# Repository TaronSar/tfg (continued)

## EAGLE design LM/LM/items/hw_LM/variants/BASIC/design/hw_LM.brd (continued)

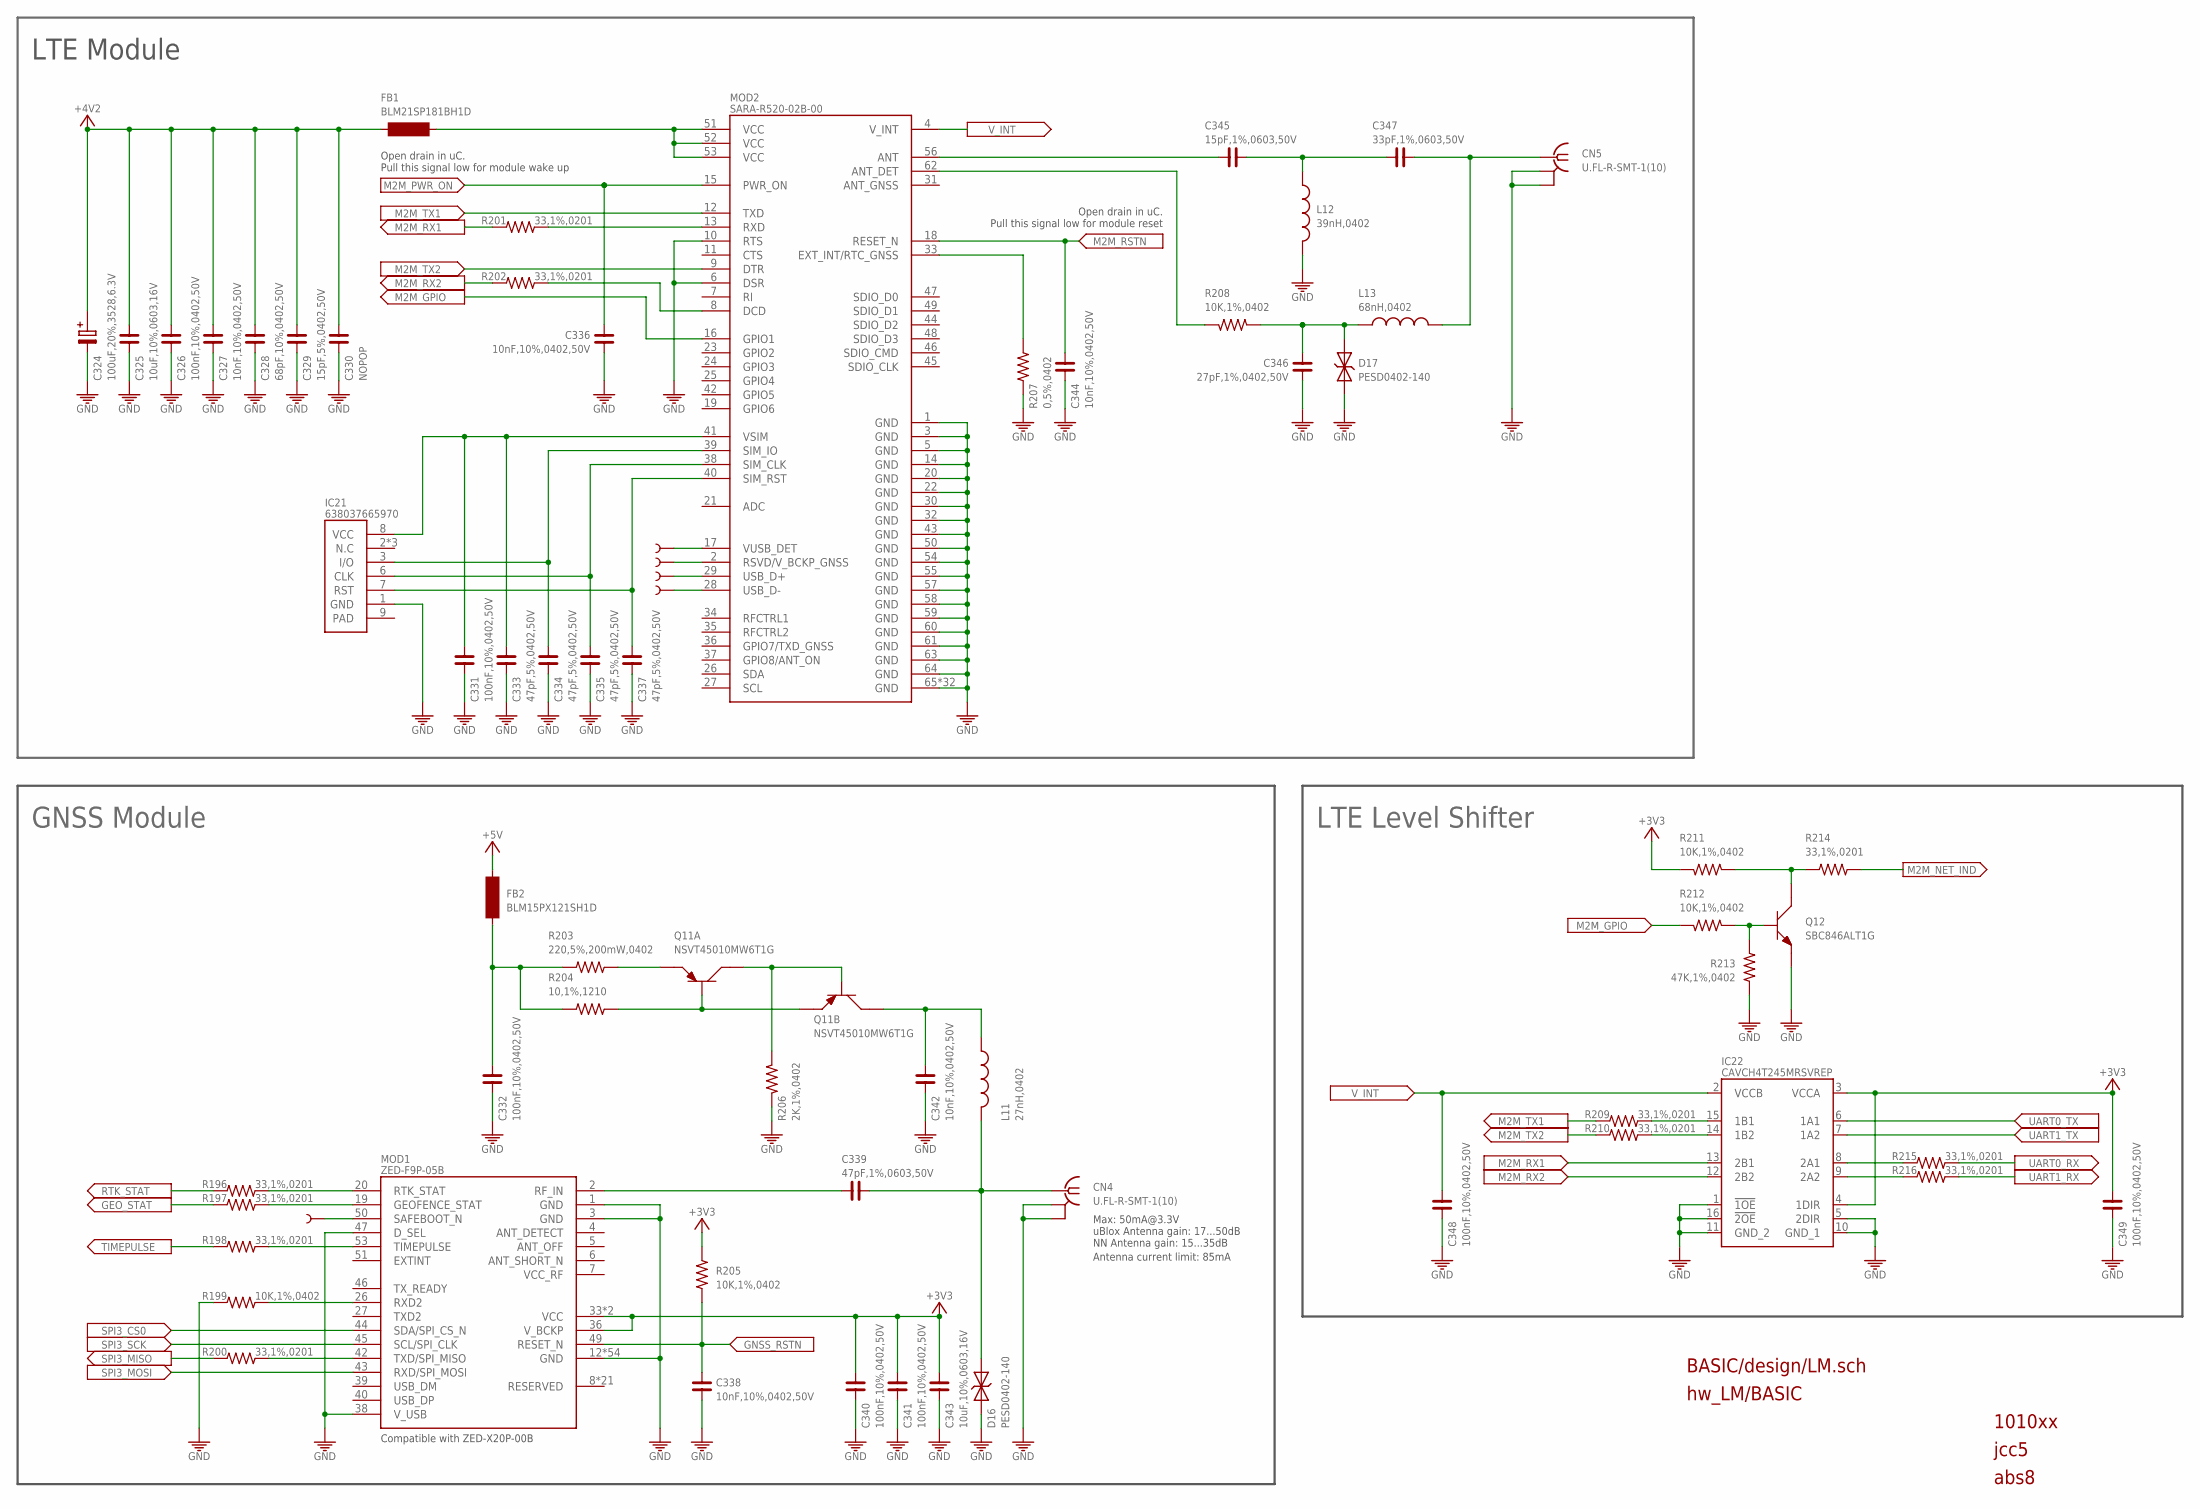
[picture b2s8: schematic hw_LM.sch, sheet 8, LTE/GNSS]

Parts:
C324: 100uF,20%,3528,6.3V; TE-B-3528
C325, C343: 10uF,10%,0603,16V; C0603
C326, C331, C332, C340, C341, C348, C349: 100nF,10%,0402,50V; C0402
C327, C336, C338, C342, C344: 10nF,10%,0402,50V; C0402
C328: 68pF,10%,0402,50V; C0402
C329: 15pF,5%,0402,50V; C0402
C330: NOPOP; C0402
C333, C334, C335, C337: 47pF,5%,0402,50V; C0402
C339: 47pF,1%,0603,50V; C0603
C345: 15pF,1%,0603,50V; C0603
C346: 27pF,1%,0402,50V; C0402
C347: 33pF,1%,0603,50V; C0603
CN4, CN5: U.FL-R-SMT-1(10); U.FL-R-SMT-1
D16, D17: PESD0402-140
FB1: BLM21SP181BH1D; L0805
FB2: BLM15PX121SH1D; L0402
IC21: 638037665970; MFF2
IC22: CAVCH4T245MRSVREP; UQFN-16
L11: 27nH,0402; L0402
L12: 39nH,0402; L0402
L13: 68nH,0402; L0402
MOD1: ZED-F9P-05B; ZED-F9P
MOD2: SARA-R520-02B-00; SARA
Q11: NSVT45010MW6T1G; SOT363
Q12: SBC846ALT1G; SOT23-3
R196, R197, R198, R200, R201, R202, R209, R210, R214, R215, R216: 33,1%,0201; R0201
R199, R205, R208, R211, R212: 10K,1%,0402; R0402
R203: 220,5%,200mW,0402; R0402
R204: 10,1%,1210; R1210
R206: 2K,1%,0402; R0402
R207: 0,5%,0402; R0402
R213: 47K,1%,0402; R0402
TP14, TP15, TP16, TP17, TP18: NOPOP; PAD.02X.02

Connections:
+3V3: C340.2, C341.2, C343.2, C349.2, IC22.3 (VCCA), IC22.4 (1DIR), MOD1.33 (VCC), MOD1.34 (VCC), MOD1.36 (V_BCKP), R205.1, R211.1; also elsewhere on the board
+4V2: C324.+, C325.2, C326.2, C327.2, C328.2, C329.2, C330.2, FB1.1; also elsewhere on the board
+5V: FB2.1; also elsewhere on the board
ANT_DC: C345.2, C347.1, L12.1
ANT_DET_SARA: MOD2.62 (ANT_DET), R208.2
ANT_OUT: C345.1, MOD2.56 (ANT)
GEO_STAT: R197.1; also elsewhere on the board
GND: C324.-, C325.1, C326.1, C327.1, C328.1, C329.1, C330.1, C331.2, C332.1, C333.2, C334.2, C335.2, C336.2, C337.2, C338.2, C340.1, C341.1, C342.1, C343.1, C344.2, C346.2, C348.1, C349.1, CN4.GND1 (GNDGPS), CN4.GND2 (GNDGPS1), CN5.GND1 (GNDGPS), CN5.GND2 (GNDGPS1), D16.P$1, D17.P$1, IC21.1 (GND), IC22.1 (!1OE), IC22.5 (2DIR), IC22.10 (GND_1), IC22.11 (GND_2), IC22.16 (!2OE), L12.2, MOD1.1 (GND), MOD1.3 (GND), MOD1.12 (GND), MOD1.14 (GND), MOD1.32 (GND), MOD1.37 (GND), MOD1.38 (V_USB), MOD1.41 (GND), MOD1.47 (D_SEL), MOD1.48 (GND), MOD1.GND1 (GND), MOD1.GND2 (GND), MOD1.GND3 (GND), MOD1.GND4 (GND), MOD1.GND5 (GND), MOD1.GND6 (GND), MOD1.GND7 (GND), MOD1.GND8 (GND), MOD1.GND9 (GND), MOD1.GND10 (GND), MOD1.GND11 (GND), MOD1.GND12 (GND), MOD1.GND13 (GND), MOD1.GND14 (GND), MOD1.GND15 (GND), MOD1.GND16 (GND), MOD1.GND17 (GND), MOD1.GND18 (GND), MOD1.GND19 (GND), MOD1.GND20 (GND), MOD1.GND21 (GND), MOD1.GND22 (GND), MOD1.GND23 (GND), MOD1.GND24 (GND), MOD1.GND25 (GND), MOD1.GND26 (GND), MOD1.GND27 (GND), MOD1.GND28 (GND), MOD1.GND29 (GND), MOD1.GND30 (GND), MOD1.GND31 (GND), MOD1.GND32 (GND), MOD1.GND33 (GND), MOD1.GND34 (GND), MOD1.GND35 (GND), MOD1.GND36 (GND), MOD1.GND37 (GND), MOD1.GND38 (GND), MOD1.GND39 (GND), MOD1.GND40 (GND), MOD1.GND41 (GND), MOD1.GND42 (GND), MOD1.GND43 (GND), MOD1.GND44 (GND), MOD1.GND45 (GND), MOD1.GND46 (GND), MOD1.GND47 (GND), MOD1.GND48 (GND), MOD2.1 (GND), MOD2.3 (GND), MOD2.5 (GND), MOD2.6 (DSR), MOD2.10 (RTS), MOD2.14 (GND), MOD2.20 (GND), MOD2.22 (GND), MOD2.30 (GND), MOD2.32 (GND), MOD2.43 (GND), MOD2.50 (GND), MOD2.54 (GND), MOD2.55 (GND), MOD2.57 (GND), MOD2.58 (GND), MOD2.59 (GND), MOD2.60 (GND), MOD2.61 (GND), MOD2.63 (GND), MOD2.64 (GND), MOD2.65 (GND), MOD2.66 (GND), MOD2.67 (GND), MOD2.68 (GND), MOD2.69 (GND), MOD2.70 (GND), MOD2.71 (GND), MOD2.72 (GND), MOD2.73 (GND), MOD2.74 (GND), MOD2.75 (GND), MOD2.76 (GND), MOD2.77 (GND), MOD2.78 (GND), MOD2.79 (GND), MOD2.80 (GND), MOD2.81 (GND), MOD2.82 (GND), MOD2.83 (GND), MOD2.84 (GND), MOD2.85 (GND), MOD2.86 (GND), MOD2.87 (GND), MOD2.88 (GND), MOD2.89 (GND), MOD2.90 (GND), MOD2.91 (GND), MOD2.92 (GND), MOD2.93 (GND), MOD2.94 (GND), MOD2.95 (GND), MOD2.96 (GND), Q12.2 (E), R199.1, R206.1, R207.1, R213.1; also elsewhere on the board
GNSS: C339.2, CN4.SIG, D16.P$2, L11.2
GNSS_RSTN: C338.1, MOD1.49 (RESET_N), R205.2; also elsewhere on the board
LTE: C347.2, CN5.SIG, L13.2
M2M_DCD: MOD2.8 (DCD), R202.2
M2M_GPIO: MOD2.16 (GPIO1), R212.2
M2M_NET_IND: R214.2; also elsewhere on the board
M2M_PWR_ON: C336.1, MOD2.15 (PWR_ON); also elsewhere on the board
M2M_RSTN: C344.1, MOD2.18 (RESET_N); also elsewhere on the board
M2M_RSVD: MOD2.2 (RSVD/V_BCKP_GNSS), TP16.P$1
M2M_RX1: IC22.13 (2B1), R201.1
M2M_RX2: IC22.12 (2B2), R202.1
M2M_RXD: MOD2.13 (RXD), R201.2
M2M_TX1: MOD2.12 (TXD), R209.1
M2M_TX2: MOD2.9 (DTR), R210.1
M2M_USB_D_N: MOD2.28 (USB_D-), TP18.P$1
M2M_USB_D_P: MOD2.29 (USB_D+), TP17.P$1
M2M_VBUS_DET: MOD2.17 (VUSB_DET), TP15.P$1
M2M_VCC: FB1.2, MOD2.51 (VCC), MOD2.52 (VCC), MOD2.53 (VCC)
unnamed: Q12.3 (C), R211.2, R214.1
unnamed: Q11.5 (B), Q11.6 (C), R206.2
unnamed: Q11.1 (E), R203.1
unnamed: MOD1.26 (RXD2), R199.2
unnamed: Q11.2 (B), Q11.4 (E), R204.1
unnamed: Q12.1 (B), R212.1, R213.2
unnamed: IC22.14 (1B2), R210.2
unnamed: IC22.15 (1B1), R209.2
unnamed: IC22.9 (2A2), R216.1
unnamed: IC22.8 (2A1), R215.1
unnamed: MOD1.20 (RTK_STAT), R196.2
unnamed: MOD1.19 (GEOFENCE_STAT), R197.2
unnamed: C332.2, FB2.2, R203.2, R204.2
unnamed: C342.2, L11.1, Q11.3 (C)
unnamed: MOD1.53 (TIMEPULSE), R198.2
unnamed: MOD1.42 (TXD/SPI_MISO), R200.2
unnamed: C346.1, D17.P$2, L13.1, R208.1
unnamed: MOD2.33 (EXT_INT/RTC_GNSS), R207.2
RF_IN: C339.1, MOD1.2 (RF_IN)
RTK_STAT: R196.1; also elsewhere on the board
SAFEBOOT_N: MOD1.50 (SAFEBOOT_N), TP14.P$1
SIM_CLK: C335.1, IC21.6 (CLK), MOD2.38 (SIM_CLK)
SIM_IO: C334.1, IC21.3 (I/O), MOD2.39 (SIM_IO)
SIM_RST: C337.1, IC21.7 (RST), MOD2.40 (SIM_RST)
SPI3_CS0: MOD1.44 (SDA/SPI_CS_N); also elsewhere on the board
SPI3_MISO: R200.1; also elsewhere on the board
SPI3_MOSI: MOD1.43 (RXD/SPI_MOSI); also elsewhere on the board
SPI3_SCK: MOD1.45 (SCL/SPI_CLK); also elsewhere on the board
TIMEPULSE: R198.1; also elsewhere on the board
UART0_RX: R215.2; also elsewhere on the board
UART0_TX: IC22.6 (1A1); also elsewhere on the board
UART1_RX: R216.2; also elsewhere on the board
UART1_TX: IC22.7 (1A2); also elsewhere on the board
VSIM: C331.1, C333.1, IC21.8 (VCC), MOD2.41 (VSIM)
V_INT: C348.2, IC22.2 (VCCB), MOD2.4 (V_INT)

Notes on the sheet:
Max: 50mA@3.3V uBlox Antenna gain: 17...50dB NN Antenna gain: 15...35dB
GNSS Module
Compatible with ZED-X20P-00B
LTE Module
Open drain in uC. Pull this signal low for module wake up
BASIC/design/LM.sch
hw_LM/BASIC
1010xx
jcc5
abs8
Open drain in uC. Pull this signal low for module reset
Antenna current limit: 85mA
LTE Level Shifter

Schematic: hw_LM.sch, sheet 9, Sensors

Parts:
C350, C355: 10uF,10%,0603,16V; C0603
C351, C352, C354, C358, C359, C360, C361, C362: 100nF,10%,0402,50V; C0402
C353, C363, C364: 10nF,10%,0402,50V; C0402
C356, C357: 2.2uF,10%,0603,16V; C0603
C365: 470nF,10%,0402,50V; C0402
FB3: BLM21PG220SN1D; L0805
IC23: AUAV-L60D-M25125-RR-N; AUAV
IC24: MAGI2C
IC25: NOPOP; LGA-14L
IC26: NOPOP; LGA-24
IC27: NOPOP; LGA-16
IC28: BMI088
L14: SEN-Z-F
L15, L16: SEN-XY-F
PCB2: RM3100; VOID
R217, R223, R226: 10K,1%,0402; R0402
R218, R219, R220, R221, R227, R228: 4.7K,1%,0402; R0402
R222: 33K,0.1%,0402; R0402
R224, R225, R235, R236, R237, R238, R239: 33,1%,0201; R0201
R229, R231, R232, R233, R234: 121,1%,0402; R0402
R230: 121,1% 0402; R0402
R240: NOPOP; R0201
R241: NOPOP; R0402

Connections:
!AUAV-SSA: IC23.4 (!SSA), R223.1
!AUAV-SSD: IC23.11 (!SSD), R226.1
+3V3: C351.1, C354.2, C355.2, C356.1, C357.1, C358.1, C359.2, C360.2, C361.2, C362.1, C363.1, C364.1, FB3.2, IC23.6 (VS), IC25.5 (VDDIO), IC25.8 (VDD), IC26.8 (VDDIO), IC26.13 (VDD), IC27.1 (VDDIO), IC27.16 (VDD), IC28.3 (VDD), IC28.11 (VDDIO), R217.2, R219.1, R221.1, R223.2, R226.2, R227.1, R228.1; also elsewhere on the board
ASM_SDO: IC25.1 (SDO/SA0), R235.1
AUAV-EOC-A: IC23.3 (EOC-A), R224.1
AUAV-EOC-D: IC23.10 (EOC-D), R225.1
AUAV-TEST: IC23.9 (TEST), R217.1
BMI_SDO1: IC28.15 (SDO1), R236.1
BMI_SDO2: IC28.10 (SDO2), R237.1
EOC_A: R224.2; also elsewhere on the board
EOC_D: R225.2; also elsewhere on the board
GND: C350.1, C351.2, C352.1, C353.1, C354.1, C355.1, C356.2, C357.2, C358.2, C359.1, C360.1, C361.1, C362.2, C363.2, C364.2, C365.2, IC23.5 (GND), IC23.8 (GND), IC24.2 (RES), IC24.5 (AVSS), IC24.19 (DVSS), IC24.20 (RES), IC25.2 (RES), IC25.3 (RES), IC25.7 (GND), IC26.11 (RESV), IC26.18 (GND), IC26.20 (RESV), IC27.9 (RESV), IC27.10 (RESV), IC27.11 (RESV), IC27.12 (RESV), IC27.13 (GND), IC27.15 (RESV), IC28.2 (NC), IC28.4 (GNDA), IC28.6 (GNDIO), IC28.7 (PS), R218.2, R220.2, R222.1, R240.2, R241.1; also elsewhere on the board
I2C1_SCL: IC23.1 (SCL/SCK), R228.2; also elsewhere on the board
I2C1_SDA: IC23.2 (SDA/MOSI), R227.2; also elsewhere on the board
I2C2_SCL: IC24.27 (SCLK/SCL), R221.2; also elsewhere on the board
I2C2_SDA: IC24.1 (MOSI/SDA), R219.2; also elsewhere on the board
IAM_SDO: IC27.4 (SA0/SDO), R238.1
ICM_SDO: IC26.9 (SDO/AD0), R239.1
MAG_3V3: C350.2, C352.2, C353.2, FB3.1, IC24.4 (AVDD), IC24.14 (DVDD), IC24.22 (I2CEN), IC24.26 (DVDD)
MAG_REXT: IC24.25 (REXT), R222.2
MAG_SA0: IC24.3 (SSN/SA0), R218.1
MAG_SA1: IC24.28 (MISO/SA1), R220.1
unnamed: C365.1, IC27.14 (REGOUT)
unnamed: IC26.19 (INT2/FSYNC), R240.1
SPI5_CS1: IC28.5 (CSB2); also elsewhere on the board
SPI5_CS3: IC28.14 (CSB1); also elsewhere on the board
SPI5_MISO: R236.2, R237.2; also elsewhere on the board
SPI5_MOSI: IC28.9 (SDA/SDI); also elsewhere on the board
SPI5_SCK: IC28.8 (SCL/SCK); also elsewhere on the board
SPI7_CS0: IC25.12 (CS); also elsewhere on the board
SPI7_CS1: IC26.22 (!CS); also elsewhere on the board
SPI7_CS2: IC27.5 (CS), R241.2; also elsewhere on the board
SPI7_MISO: R235.2, R238.2, R239.2; also elsewhere on the board
SPI7_MOSI: IC25.14 (SDI/SDA), IC26.24 (SDA/SDI/SDIO), IC27.3 (SDA/SDI); also elsewhere on the board
SPI7_SCK: IC25.13 (SCK/SCL), IC26.23 (SCL/SCLK), IC27.2 (SCL/SPC); also elsewhere on the board
XDRV_N: IC24.18 (XDRVN), R234.2
XDRV_P: IC24.15 (XDRVP), R233.2
XIN_N: IC24.17 (XINN), L16.P$3 (2), L16.P$4 (2), R234.1
XIN_P: IC24.16 (XINP), L16.P$1 (1), L16.P$2 (1), R233.1
YDRV_N: IC24.13 (YDRVN), R232.2
YDRV_P: IC24.10 (YDRVP), R231.2
YIN_N: IC24.12 (YINN), L15.P$3 (2), L15.P$4 (2), R232.1
YIN_P: IC24.11 (YINP), L15.P$1 (1), L15.P$2 (1), R231.1
ZDRV_N: IC24.9 (ZDRVN), R230.2
ZDRV_P: IC24.6 (ZDRVP), R229.2
ZIN_N: IC24.8 (ZINN), L14.N (2), L14.P$1 (2), R230.1
ZIN_P: IC24.7 (ZINP), L14.P (1), L14.P$3 (1), R229.1

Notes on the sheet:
IMUs
Magnetometer
Differential Pressure Sensor
Address:0x20
Design Note: Orientation for Z axis is important. Marking shall be on negative pin. Orientation for XY axes are irelevant.
BASIC/design/LM.sch
hw_LM/BASIC
1010xx
jcc5
abs8
Address Abs: 0x27
Address Diff: 0x26
If POP use ASM330LHHXG1
If POP use ICM-40609-D
If POP use IAM-20680HT

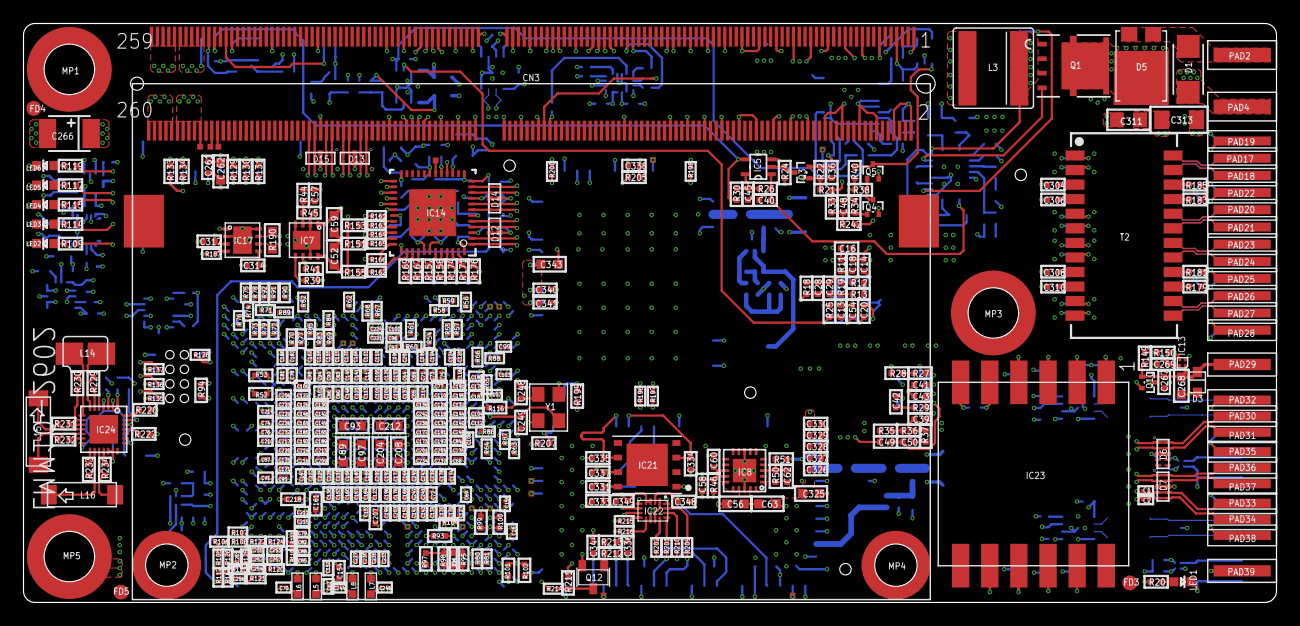
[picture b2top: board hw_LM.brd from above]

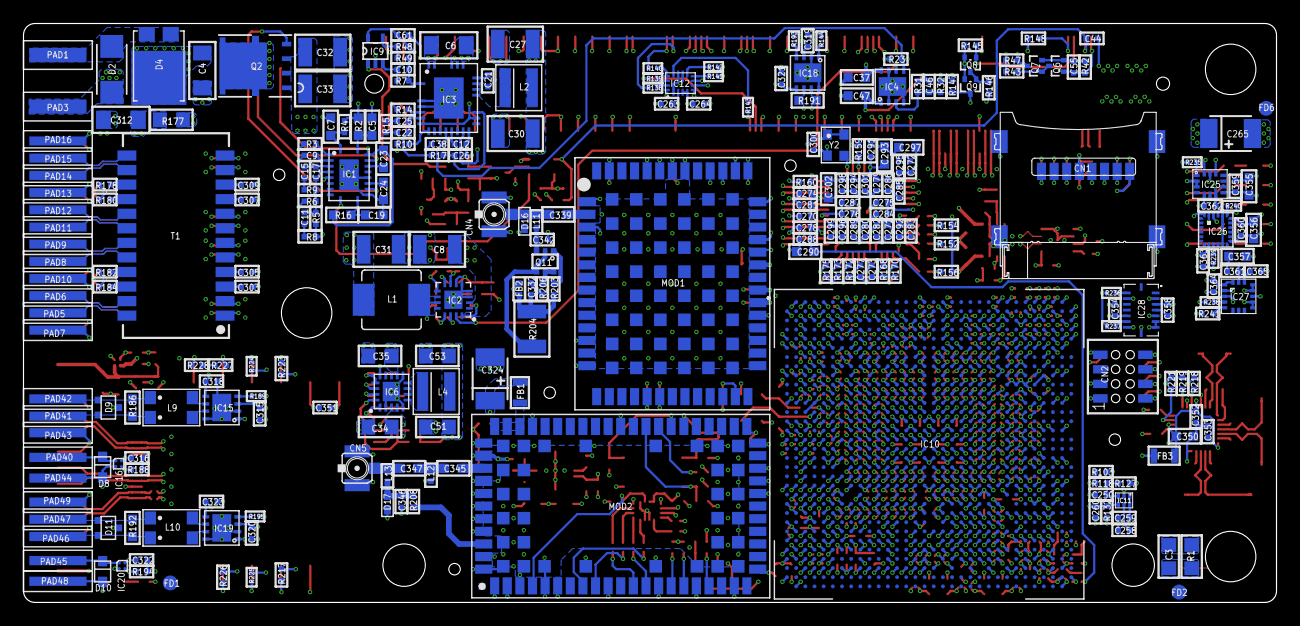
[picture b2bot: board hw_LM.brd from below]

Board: 10 copper layers, 109.3 x 50.5 mm, 782 parts (270 on the bottom side), 413 nets.

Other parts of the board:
U$3: A5-PCB
U$4: A5-PCB_MIRROR

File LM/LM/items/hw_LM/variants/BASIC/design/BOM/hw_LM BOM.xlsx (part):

Version | 101010
Schematics Name | hw_LM.sch
Designer Name | Embention Sistemas Inteligentes S.A.
Date | 2026-01-08
QUANTITY | VALUE | DEVICE | PARTS | P/Ns
28 | 100nF,10%,0201,16V | C_0201 | C1, C125, C129, C133, C136, C137, C141, C145, C148, C151, C152, C153, C156, C15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 | GRT033C71C104KE01J | GRT033C71C104KE01D
2 | 100nF,10%,0402,16V | C_0402 | C259, C261 | GCM155R71C104KA55D
63 | 100nF,10%,0402,50V | C_0402 | C10, C13, C20, C21, C263, C264, C267, C270, C271, C272, C274, C275, C276, C279,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 | GCM155R71H104KE02D | GCM155L8EH104KE07D
3 | 100nF,10%,0603,100V | C_0603 | C23, C5, C7 | HMJ107BB7104KAHT | MCJCH168BB7104KTPA01
2 | 100uF,20%,0805,4V | C_0805 | C51, C53 | GRM21BC80G107ME15L | GRM21BC80G107ME15K | CL21X107MRYN3WE
5 | 100uF,20%,1210,6.3V | C_1210 | C27, C30, C31, C32, C33 | GRT32ER60J107ME13L
3 | 100uF,20%,3528,6.3V | C-PR-SMD-TE-B | C265, C266, C324 | T491B107M006ATAUTO
55 | 10nF,10%,0201,10V | C_0201 | C102, C106, C107, C112, C115, C132, C143, C144, C158, C159, C163, C166, C167, C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 | CGA1A2X7R1A103K030BA | GCM033R71A103KA03J
17 | 10nF,10%,0402,50V | C_0402 | C15, C273, C277, C288, C291, C295, C301, C327, C336, C338, C342, C344, C353, C3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 | CGA2B3X8R1H103K050BB
3 | 10pF,1%,0402,50V | C_0402 | C248, C249, C25 | GCQ1555C1H100FB01D
10 | 10pF,5%,0201,50V | C_0201 | C134, C138, C142, C146, C149, C165, C169, C173, C177, C181 | GA1A2C0G1H100D030BA | GCM0335C1H100JA16D | GRT0335C1H100JA02D
6 | 10uF,10%,0603,16V | C_0603 | C268, C325, C343, C350, C355, C56 | GRT188R61C106KE13D
4 | 10uF,20%,0603,10V | C_0603 | C290, C293, C297, C302 | GRT188C81A106ME13D
1 | 15nF,10%,0402,50V | C_0402 | C258 | GCM155R71H153KA55D
1 | 15pF,1%,0603,50V | C_0603 | C345 | 06035U150FAT2A
1 | 15pF,5%,0402,50V | C_0402 | C329 | C0402C150J5GACAUTO | GCM1555C1H150JA16D
1 | 180pF,5%,0402,50V | C_0402 | C17 | AC0402JRNPO9BN181 | GCM1555C1H181JA16J
23 | 1nF,10%,0201,25V | C_0201 | C100, C110, C114, C118, C119, C122, C124, C126, C130, C147, C150, C155, C179, C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 | CGA1A2X7R1E102K030BA | AC0201KRX7R8BB102
1 | 1nF,10%,0402,50V | C_0402 | C250 | C0402C102K5GECAUTO7411
2 | 1nF,10%,1206,2KV | C_1206 | C312, C313 | C1206C102KGRACAUTO
14 | 1uF,10%,0402,25V | C_0402 | C269, C278, C281, C282, C284, C285, C286, C287, C289, C292, C298, C299, C316, C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 | GRT155R61E105KE01D
1 | 1uF,10%,0603,16V | C_0402 | C26 | C0603C105K4RACAUTO
60 | 1uF,20%,0201,6.3V | C_0201 | C101, C103, C104, C105, C108, C109, C111, C113, C116, C117, C120, C121, C123, C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 | GRT033D70J105ME13D | KAM03CT70J105KH
2 | 2.2nF,10%,0402,50V | C_0402 | C11, C22 | 04025C222K4T2A | AC0402KPX7R9BB222
4 | 2.2uF,10%,0402,16V | C_0402 | C154, C161, C207, C218 | GRT155C81C225KE13D
8 | 2.2uF,10%,0603,16V | C_0603 | C24, C262, C356, C357, C37, C47, C52, C59 | CGA3E1X7S1C225K080AC | GRT188C71C225KE13D | CGA3E1X7S1C225K080AE
1 | 2.7pF,C0G,0402,50V | C_0402 | C50 | GJM1555C1H2R7CB01D
1 | 22nF,10%,0402,50V | C_0402 | C16 | C0402C223K5RECAUTO
1 | 22pF,5%,0603,100V | C_0603 | C19 | C0603C220J1GACAUTO | GCM1885C2A220JA16D
7 | 22uF,20%,0603,6.3V | C_0603 | C204, C208, C212, C63, C89, C93, C97 | GRT188C80J226ME13D
2 | 22uF,20%,0805,6.3V | C_0805 | C34, C35 | GRT21BD70J226ME13L | KAM21AT70J226MU
2 | 27pF,1%,0402,50V | C_0402 | C346, C49 | GCQ1555C1H270FB01D
1 | 3.3nF,10%,0402,50V | C_0402 | C14 | GCM155R71H332KA37J
1 | 33pF,1%,0603,50V | C_0603 | C347 | 06035U330FAT2A
1 | 33pF,5%,0402,50V | C_0402 | C43 | GCM1555C1H330JA16D
1 | 390pF,10%,0402,50V | C_0402 | C42 | GCM155R71H391KA37D
2 | 4.7nF,10%,0805,1kV | C_0805 | C3, C311 | C0805V472KDRACAUTO | C0805C472KDRACAUTO
2 | 4.7uF,20%,1206,100V | C_1206 | C4, C6 | GRM31CC72A475ME11L
7 | 470nF,10%,0201,16V | C_0201 | C251, C252, C253, C254, C255, C256, C257 | MSASE063BB5474KFNB33
1 | 470nF,10%,0402,50V | C_0402 | C365 | GRM155R61H474KE11D | UMK105ABJ474KV-F
1 | 47pF,1%,0603,50V | C_0603 | C339 | 06035U470FAT2A
4 | 47pF,5%,0402,50V | C_0402 | C333, C334, C335, C337 | GCM1555C1H470JA16D
1 | 47uF,10%,1210,10V | C_1210 | C8 | GCM32EC71A476KE02K
1 | 56nF,10%,0402,16V | C_0402 | C9 | GCM155R71C563KA55J
2 | 68pF,10%,0402,50V | C_0402 | C18, C328 | C0402C680J5GACAUTO
1 | 2309409-1 | 2309409-1 | CN3 | 2309409-1
1 | 47219-2001 | SD-LATCH | CN1 | 47219-2001
1 | CLP-104-02-F-D-BE | CLP-104-02-F-D-BE | CN2 | CLP-104-02-F-D-BE
2 | U.FL-R-SMT-1(10) | U.FL-R-SMT-1 | CN4, CN5 | U.FL-R-SMT-1(10)
3 | AQ05C-01FTG | AQ4020-01FTG | D10, D3, D8 | AQ05C-01FTG
1 | KB_DELPS2.12-QHRI-24-Z555 | LED0603 | LED4 | KB_DELPS2.12-QHRI-24-Z555
1 | KW_EELP41.RU-S1U1-3K6L-3X4X-5-R18 | LED0603 | LED6 | KW EELP41.RU-S1U1-3K6L-3X4X-5-R18
2 | PESD0402-140 | PESD0402-140 | D16, D17 | PESD0402-140
2 | SMA6J64CA | SZ1SMA36CAT3G | D1, D2 | SMA6J64CA
1 | SML-D12D8WT86C | LED0603 | LED5 | SML-D12D8WT86C
1 | SML-D12P8WT86C | LED0603 | LED3 | SML-D12P8WT86C
2 | SML-D12V8WT86C | LED0603 | LED1, LED2 | SML-D12V8WT86C
2 | STPST8H100SFY | STPST8H100SFY | D4, D5 | STPST8H100SFY
6 | TPD4E05U06QDQARQ1 | TPD4E05U06QDQARQ1 | D12, D13, D14, D15, D6, D7 | TPD4E05U06QDQARQ1
2 | VCAN26C2-03GHE3-08 | VCAN26C2-03GHE3-08 | D11, D9 | VCAN26C2-03GHE3-08
1 | BLM15PX121SH1D | BLM15PX121SH1D | FB2 | BLM15PX121SH1D
1 | BLM21PG220SN1D | BLM21PG300SN1D | FB3 | BLM21PG220SN1D
1 | BLM21SP181BH1D | BLM21PG300SN1D | FB1 | BLM21SP181BH1D
4 | MPZ1608Y101BTD25 | MPZ1608Y101BTD25 | L5, L6, L7, L8 | MPZ1608Y101BTD25
1 | AUAV-L60D-M25125-RR-N | AUAV | IC23 | AUAV-L60D-M25125-RR-N
1 | BMI088 | BMI088 | IC28 | BMI088
1 | CAHCT1G32QDCKRQ1 | SN74AHCT1G32Q1 | IC9 | CAHCT1G32QDCKRQ1
2 | CAVCH4T245MRSVREP | SN74AVCH4T245-EP | IC12, IC22 | CAVCH4T245MRSVREP
1 | DP83867ERGZT | DP83867ERGZ | IC14 | DP83867ERGZT
1 | ECS-2520MVQ-250-CN-TR | ECS-2520MVQ-250-CN-TR | Y2 | ECS-2520MVQ-250-CN-TR
1 | LM5146QRGYRQ1 | LM5146-Q1 | IC1 | LM5146QRGYRQ1
1 | LTC3310SEV#WPBF | LTC3310S | IC6 | LTC3310SEV#WPBF
1 | LTC7103MPUHE#PBF | LTC7103IUHE | IC3 | LTC7103MPUHE#PBF
1 | MAGI2C | MAGI2C | IC24 | MAGI2C INCLUDED ON 90053
1 | RM3100 | EXTERNAL-PCB-COMPONENTS | PCB2 | 90053.0
1 | S32E288ABCAAMJGT | S32E288AACAAMJGR | IC10 | S32E288ABCAAMJGT
1 | SARA-R520-02B-00 | SARA-R52 | MOD2 | SARA-R520-02B-00
1 | SN74LVC1G08QDCKRQ1 | SN74LVC1G08QDCKRQ1 | IC5 | SN74LVC1G08QDCKRQ1
4 | TCAN1462VDRBRQ1 | TCAN1462V-Q1VSON-8 | IC15, IC17, IC18, IC19 | TCAN1462VDRBRQ1
3 | TPS22912CYZVR | TPS2291XX | IC13, IC16, IC20 | TPS22912CYZVR
1 | TPS3897ADRYT | TPS3895ADRY | IC11 | TPS3897ADRYT
1 | TPS57112CQRTERQ1 | TPS57112C-Q1 | IC2 | TPS57112CQRTERQ1
1 | TPS74501PQWDRBRQ1 | TPS745-Q1 | IC7 | TPS74501PQWDRBRQ1
1 | TPS74525PQWDRBRQ1 | TPS745-Q1 | IC4 | TPS74525PQWDRBRQ1
1 | TPS7A5301QRGRRQ1 | TPS7A5201QRGRRQ1 | IC8 | TPS7A5301QRGRRQ1
1 | ZED-F9P-05B | ZED-F9P | MOD1 | ZED-F9P-05B
2 | 1812CAN-113NRC | 1812CAN | L10, L9 | 1812CAN-113NRC
1 | 2.2uH,20%,5.5A | XAL4020 | L2 | XAL4020-222MEC
1 | 220nH,20%,16.8A | XAL4020 | L4 | XAL4020-221MEC
1 | 27nH,0402 | L_0402 | L11 | LQG15HH27NJ02D | LQG15HZ27NJ02D
1 | 39nH,0402 | L_0402 | L12 | LQG15HS39NJ02D
1 | 4.7uH,20%,9A | XAL7030472 | L3 | XAL7030-472MEC
1 | 6.8uH,20%,2.8A | IHLP2020CZER220M11 | L1 | IHLP2020BZER6R8M5A
1 | 68nH,0402 | L_0402 | L13 | LQG15HS68NJ02D
2 | 749020112B | 749020112B | T1, T2 | 749020112B
2 | SEN-XY-F | SEN-XY-F | L15, L16 | SEN-XY-F INCLUDED ON 90053
1 | SEN-Z-F | SEN-Z-F | L14 | SEN_Z_F INCLUDED ON 90053
1 | 638037665970 | ESIM | IC21 | 6.3803766597E11
2 | 9774027151R | WA-SMSI_9774XXX151_9774027151R | MP2, MP4 | 9774027151R
3 | 9774090360R | 9774050360R | MP1, MP3, MP5 | 9774090360R
1 | ECS-400-8-33Q-ADS-TR | ECS-250-18-33Q-DS-TR3 | Y1 | ECS-400-8-33Q-ADS-TR
1 | LMM10-2602 | EXTERNAL-PCB-COMPONENTS | PCB1 | LMM10-2602
3 | 0,5%,0402 | R_0402 | R116, R148, R207 | ERJ-2GE0R00X
6 | 1.5K,1%,0402 | R_0402 | R109, R114, R115, R117, R119, R159 | ERJ-2RKF1501X
17 | 100K,1%,0402 | R_0402 | R146, R147, R149, R150, R188, R194, R22, R24, R26, R34, R38, R4, R40, R42, R43,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 | ERJ-2RKF1003X
28 | 10K,1%,0402 | R_0402 | R100, R102, R103, R129, R132, R15, R199, R205, R208, R211, R212, R217, R223, R2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 | ERJ-2RKF1002X
1 | 10,1%,1210 | R_1210 | R204 | CRCW121010R0FKEAHP
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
